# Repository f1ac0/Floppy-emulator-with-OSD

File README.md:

# Floppy emulator with OSD
This is a fusion of a "Gotek" and a "Bluepill" that can provide both FlashFloppy and FF_OSD on a single board. Thank you to Keir Fraser for his firmware https://github.com/keirf/FlashFloppy, and to the chinese people for the original device.

Thanks to the OSD and Amiga keyboard support, LCD/OLED display or buttons are no longer necessary and the device can be almost completely hidden inside Amiga computers, without damaging their case. It is still possible to install a display and buttons, though.

This board also has something special : when connected to an "Amiga dual floppy selector" board, it can daisy-chain between the original floppy drive and the motherboard. In this configuration, the OSD let you choose dynamically which drive is DF0 and DF1. Thanks to this you can enjoy both your original games on floppies and disk images on USB or SDcard !

# Disclaimer
This is a hobbyist project, it comes with no warranty and no support. Also remember that the Amiga machines are about 30 years old and may fail because of such hardware expansions.

This version is not endorsed by the author of FlashFloppy, please don't bother him with issues you might have because of it.

I publish my work under the CC-BY-NC-SA license. The content of this repository is the result of weeks of work, requiring investment in tools, parts, prototypes, and risky tests on his own equipment. For this reason the author does not want third parties to sell products and keep all the profit, usually without even offering support to their customers. If you see people selling this without the consent of the author, don't buy from them.

My modifications to the FF_OSD source are under "the unlicense", like the original code.

If you find it useful and want to reward me : I am always looking for Amiga/Amstrad CPC hardware to repair and hack, please contact me.

# BOM
- 1x STM32F105RBT6
- 1x STM32F103C8T6
- 1x 74LS07D
- 1x 3.3v LDO, either SPX3819M5-L-3-3 or XC6206P332MR or equivalent
- 2x 8MHz HC-49 crystals
- 3x 10uF 0805 capacitors
- 9x 100nF 0805 capacitors
- 4x 22pf 0805 capacitors
- 2x 1k 4x0603 resistor arrays
- 3x 4k7 0805 resistors
- 1x 270 ohm 0805 resistor
- 2x 22 ohm 0805 resistors
- optional for activity LED : 1x 0805 resistor and LED
- 1x 2x17 pins, socket or header, see below. Remove pin 3 which is a key.
- optional for drive daisy-chain : 1x 2x17 pins header or socket. You might choose 90° angled type. Remove pin 3 which is a key.
- 1x USB A Female Socket, type G54
- 1x vertical floppy power connector or 1x4 pin header
- jumpers or wire for DS0/DS1 selection
- pin headers or wires for keyboard, video, drive selection, piezo transducer, SD-card, buttons, rotary encoder, display

Other boards you may use with this "Floppy emulator with OSD":
- [Amiga-dual-floppy-selector](https://github.com/f1ac0/Amiga-dual-floppy-selector) to keep your mechanical drive
- [A600-1200KeyboardSocket](https://github.com/f1ac0/Breakout-and-simple-connector-boards) to pick the keyboard signals on an A600 or A1200
- [USB_A or microSD breakout](https://github.com/f1ac0/Breakout-and-simple-connector-boards) to make the flash memory accessible from outside the system

# Making it
Components are SMD, and have quite thin pin pitch. You need to know what you are doing.

You may choose to install the USB and/or SD connector on a remote board, to make them accessible through trapdoors or openings in the case. You may solder buttons, rotary encoder, LED, display and piezo transducer.

Check for shorts at least between 5V, 12V and GND traces before applying power !

The programming port do not need to be soldered since it needs to be programmed just once : you can just hold it in place during the few seconds required for programming.

If you plan to use the "Amiga dual floppy selector":
- on the hardware side, install female pin socket inside P1 and J11 on the bottom of the PCB. This way they will plug on the pin headers of the selector. Otherwise if you plan to use only ribbon cables, then populate them with pin headers on the top. 
- on the software side, you need to compile FF\_OSD from source, with the small modifications proposed in this repository. Use `patch -ru -d FF_OSD-master  < patch` to apply them. FlashFloppy does not require any modification.

To program the F103 uC then the F105 uC, I personally use a STLINK clone dongle with the stlink tool : https://github.com/stlink-org/stlink. Each uC has its own SWDIO/SWDCLK pins.

To connect the wires to components on the A500 motherboard without soldering on it, here is a tip :
- Take a metal pin from the female 2.54mm pin socket, which is shaped as a lyre. The one you removed from pin 3 for example.
- Solder the wire on the pin, where you normally solder it.
- Place the pin inside heat-shrink tube, with only 1mm of metal uncovered from the tips of the lyre.
- Snap the tip on the lyre on the component where you want to connect.

# Using it
- Connect the device either on top of an "Amiga dual floppy selector", or to the floppy ribbon cable and power plug
- When using the "Amiga dual floppy selector", if you plan to use a second drive, then connect its ribbon cable to the daisy chain connector of the Floppy emulator. Connect the drive power cable on the selector.
- Connect CSYNC, KB_CLOCK and KB_DATA to the motherboard as explained in FF_OSD wiki.
- Connect VIDEO to the motherboard. The 270 ohm resistor is now embedded on the latest revision of the board.
- Insert the USB thumb drive or SD-card
- Turn on the Amiga, enjoy.

To change the drives configuration using the "Amiga dual floppy selector" :
- First you should eject all floppies to prevent confusion of the OS.
- Go to the FF_OSD config menu, change the Drive config setting accordingly. Then Use or Save the new settings.
- If you changed from one to two or two to one drive, then you need to reboot for the second drive to be identified or ignored correctly.

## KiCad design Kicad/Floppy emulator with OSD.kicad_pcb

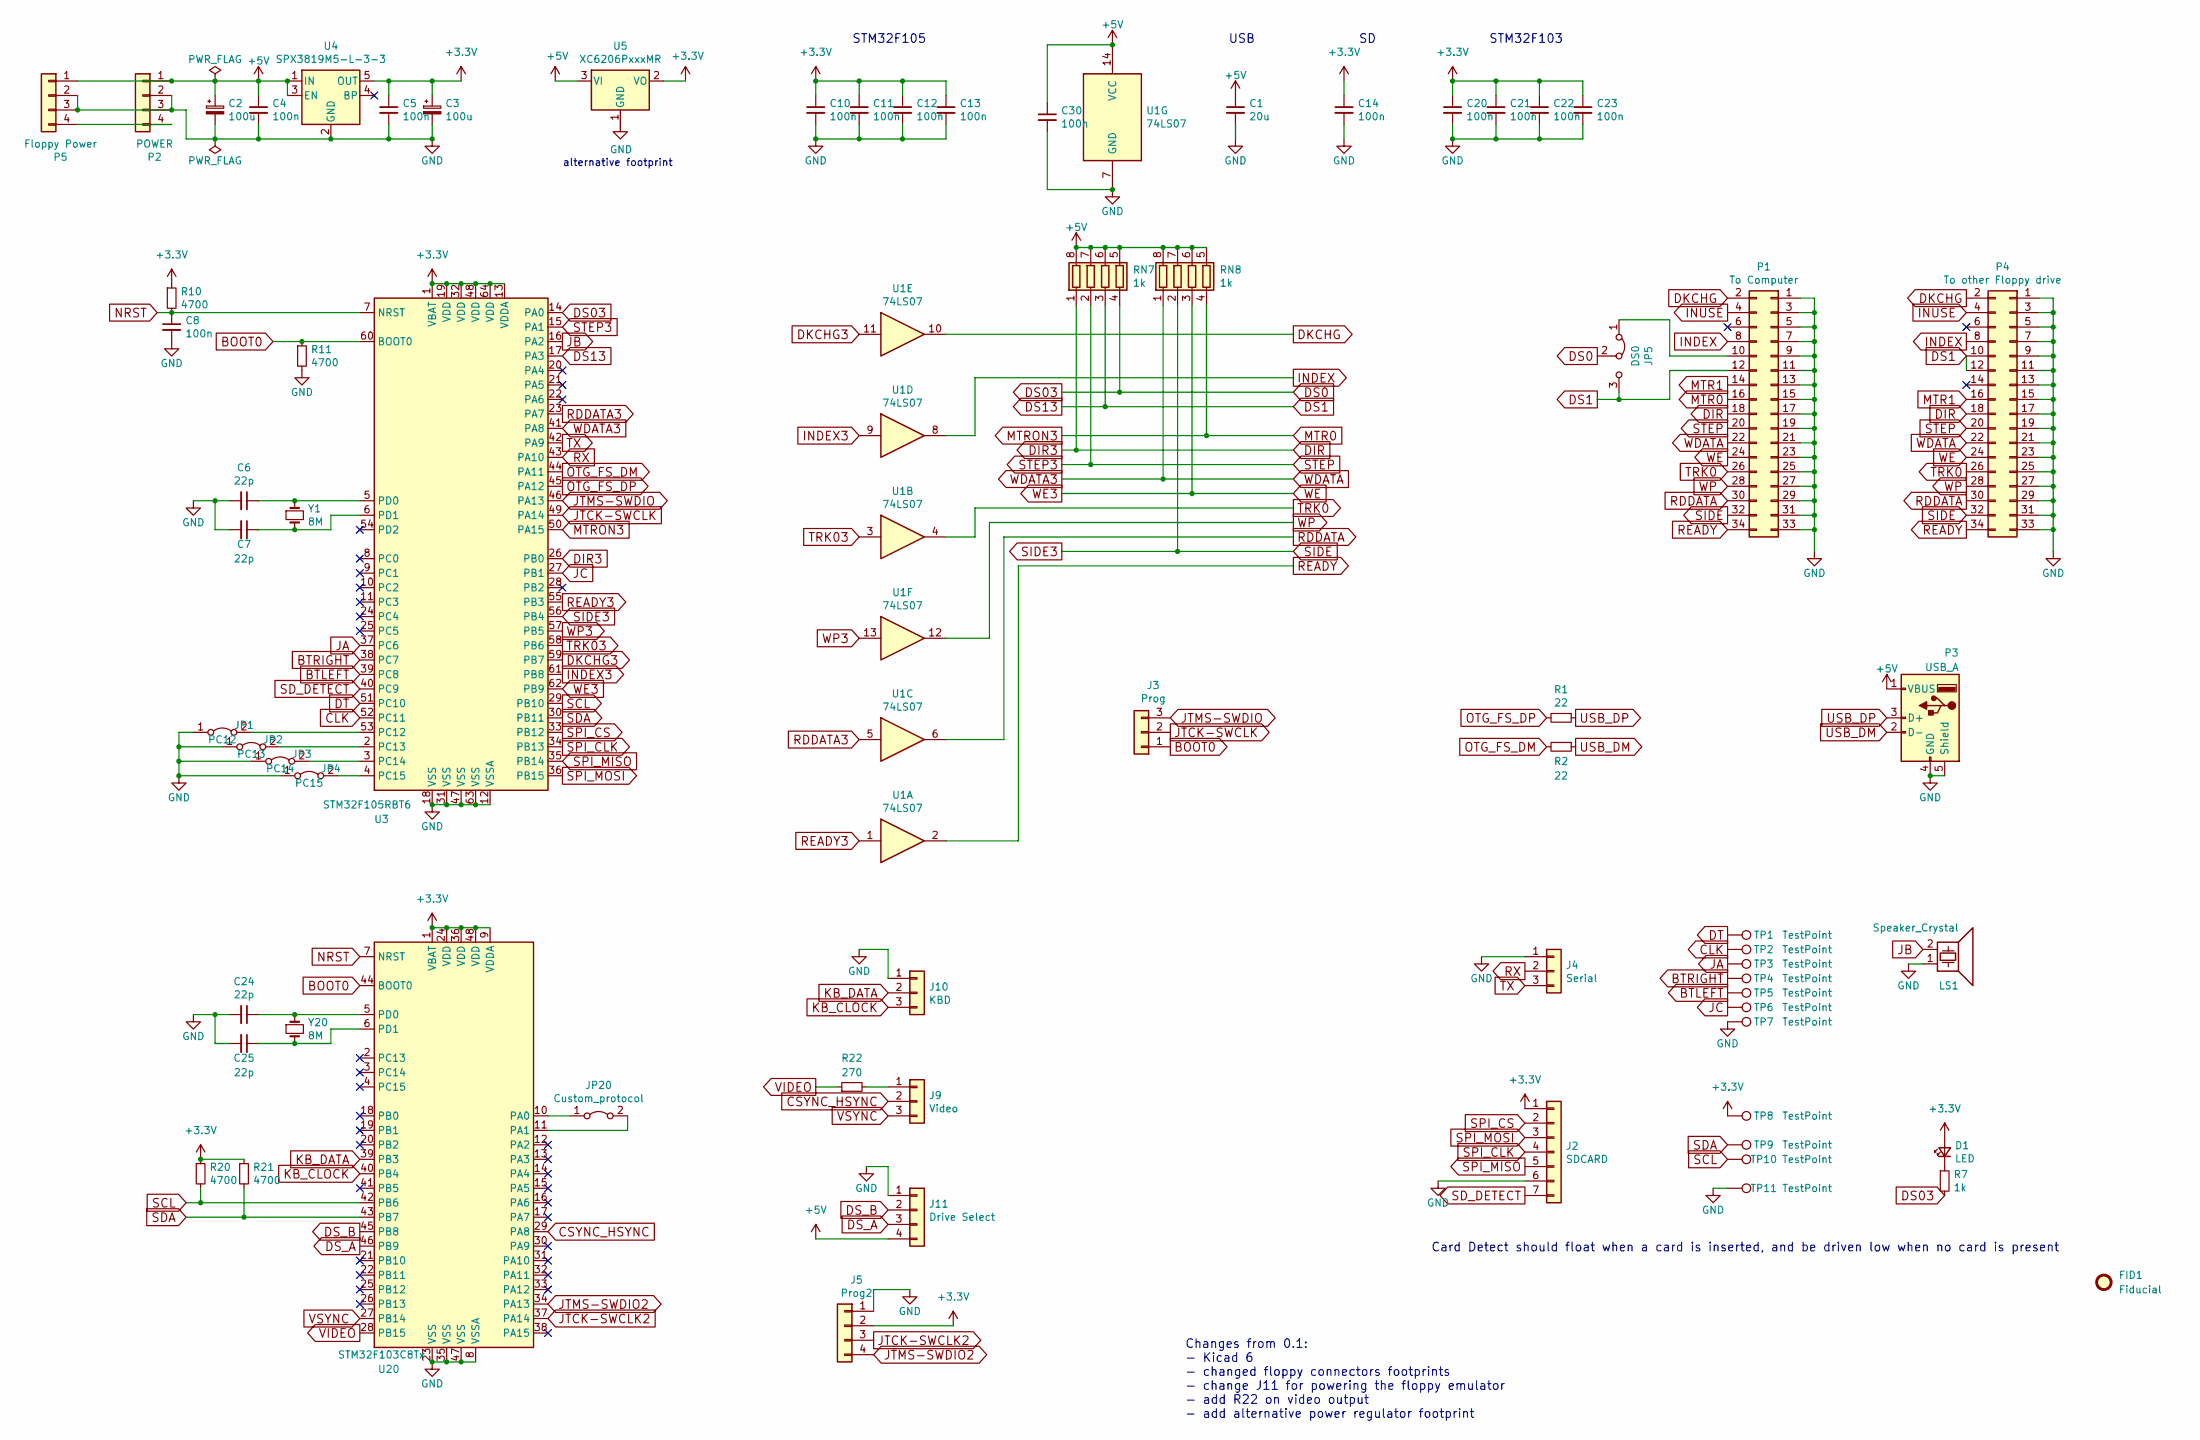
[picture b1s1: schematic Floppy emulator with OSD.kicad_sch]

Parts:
C1: 20u; C_0805_2012Metric
C2, C3: 100u; CP_Radial_D5.0mm_P2.50mm
C4, C5, C8, C10, C11, C12, C13, C14, C20, C21, C22, C23, C30: 100n; C_0805_2012Metric
C6, C7, C24, C25: 22p; C_0805_2012Metric
D1: LED; PinHeader_1x02_P2.54mm_Vertical
FID1: Fiducial; CC_BY_NC_SA_long_silkscreen
J2: SDCARD; PinHeader_1x07_P2.54mm_Vertical
J3: Prog; PinHeader_1x03_P2.54mm_Vertical
J4: Serial; PinHeader_1x03_P2.54mm_Vertical
J5: Prog2; PinHeader_1x04_P2.54mm_Vertical
J9: Video; PinHeader_1x03_P2.54mm_Vertical
J10: KBD; PinHeader_1x03_P2.54mm_Vertical
J11: Drive Select; PinSocket_1x04_P2.54mm_Vertical
JP1: PC12; SolderJumper-2_P1.3mm_Bridged_RoundedPad1.0x1.5mm
JP2: PC13; SolderJumper-2_P1.3mm_Bridged_RoundedPad1.0x1.5mm
JP3: PC14; SolderJumper-2_P1.3mm_Bridged_RoundedPad1.0x1.5mm
JP4: PC15; SolderJumper-2_P1.3mm_Bridged_RoundedPad1.0x1.5mm
JP5: DS0; PinHeader_1x03_P2.54mm_Vertical
JP20: Custom_protocol; SolderJumper-2_P1.3mm_Bridged_RoundedPad1.0x1.5mm
LS1: Speaker_Crystal; PinHeader_1x02_P2.54mm_Vertical
P1: To Computer; PinSocket_2x17_P2.54mm_Vertical
P2: POWER; Floppy_Power_1x04x2.50mm_Vertical
P3: USB_A; USB_A_female_THT_G54
P4: To other Floppy drive; PinHeader_2x17_P2.54mm_Vertical
P5: Floppy Power; PinHeader_1x04_P2.54mm_Vertical
R1, R2: 22; R_0805_2012Metric
R7: 1k; R_0805_2012Metric
R10, R11, R20, R21: 4700; R_0805_2012Metric
R22: 270; R_0805_2012Metric
RN7, RN8: 1k; R_Array_Convex_4x0603
TP1, TP2, TP3, TP4, TP5, TP6, TP7, TP8, TP9, TP10, TP11: TestPoint; TestPoint_THTPad_D1.7mm_Drill1.0mm
U1: 74LS07; SOIC-14_3.9x8.7mm_P1.27mm
U3: STM32F105RBT6; LQFP-64_10x10mm_P0.5mm
U4: SPX3819M5-L-3-3; SOT-23-5
U5: XC6206PxxxMR; SOT-23
U20: STM32F103C8Tx; LQFP-48_7x7mm_P0.5mm
Y1, Y20: 8M; Crystal_HC49-4H_Vertical

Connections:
+3.3V: C3.1, C5.1, C10.1, C11.1, C12.1, C13.1, C14.1, C20.1, C21.1, C22.1, C23.1, D1.2 (A), J2.1, J5.2, R10.1, R20.1, R21.1, TP8.1, U3.1 (VBAT), U3.13 (VDDA), U3.19 (VDD), U3.32 (VDD), U3.48 (VDD), U3.64 (VDD), U4.5 (OUT), U5.2 (VO), U20.1 (VBAT), U20.9 (VDDA), U20.24 (VDD), U20.36 (VDD), U20.48 (VDD)
+5V: C1.1, C2.1, C4.1, C30.1, J11.4, P2.1, P3.1 (VBUS), P5.1, RN7.5 (R4.2), RN7.6 (R3.2), RN7.7 (R2.2), RN7.8 (R1.2), RN8.5 (R4.2), RN8.6 (R3.2), RN8.7 (R2.2), RN8.8 (R1.2), U1.14 (VCC), U4.1 (IN), U4.3 (EN), U5.3 (VI)
BOOT0: J3.1, R11.1, U3.60 (BOOT0), U20.44 (BOOT0)
BTLEFT: TP5.1, U3.39 (PC8)
BTRIGHT: TP4.1, U3.38 (PC7)
CLK: TP2.1, U3.52 (PC11)
CSYNC_HSYNC: J9.2, U20.29 (PA8)
DIR: P1.18, P4.18, RN7.1 (R1.1), U3.26 (PB0)
DKCHG: P1.2, P4.2, U1.10
DKCHG3: U1.11, U3.59 (PB7)
DS0: JP5.2 (C), R7.2, RN7.4 (R4.1), U3.14 (PA0)
DS1: JP5.3 (B), P1.12, P4.10, P4.12, RN7.3 (R3.1), U3.17 (PA3)
DS_A: J11.3, U20.46 (PB9)
DS_B: J11.2, U20.45 (PB8)
DT: TP1.1, U3.51 (PC10)
GND: C1.2, C2.2, C3.2, C4.2, C5.2, C6.2, C7.2, C8.2, C10.2, C11.2, C12.2, C13.2, C14.2, C20.2, C21.2, C22.2, C23.2, C24.2, C25.2, C30.2, J2.6, J4.1, J5.1, J10.1, J11.1, JP1.1 (A), JP2.1 (A), JP3.1 (A), JP4.1 (A), LS1.1, P1.1, P1.3, P1.5, P1.7, P1.9, P1.11, P1.13, P1.15, P1.17, P1.19, P1.21, P1.23, P1.25, P1.27, P1.29, P1.31, P1.33, P2.2, P2.3, P3.4 (GND), P3.5 (Shield), P4.1, P4.3, P4.5, P4.7, P4.9, P4.11, P4.13, P4.15, P4.17, P4.19, P4.21, P4.23, P4.25, P4.27, P4.29, P4.31, P4.33, P5.2, P5.3, R11.2, TP7.1, TP11.1, U1.7 (GND), U3.12 (VSSA), U3.18 (VSS), U3.31 (VSS), U3.47 (VSS), U3.63 (VSS), U4.2 (GND), U5.1 (GND), U20.8 (VSSA), U20.23 (VSS), U20.35 (VSS), U20.47 (VSS)
INDEX: P1.8, P4.8, U1.8
INDEX3: U1.9, U3.61 (PB8)
INUSE: P1.4, P4.4
JA: TP3.1, U3.37 (PC6)
JB: LS1.2, U3.16 (PA2)
JC: TP6.1, U3.27 (PB1)
JTCK-SWCLK: J3.2, U3.49 (PA14)
JTCK-SWCLK2: J5.3, U20.37 (PA14)
JTMS-SWDIO: J3.3, U3.46 (PA13)
JTMS-SWDIO2: J5.4, U20.34 (PA13)
KB_CLOCK: J10.3, U20.40 (PB4)
KB_DATA: J10.2, U20.39 (PB3)
MTR0: P1.16, RN8.4 (R4.1), U3.50 (PA15)
MTR1: P1.14, P4.16
NRST: C8.1, R10.2, U3.7 (NRST), U20.7 (NRST)
unnamed: C6.1, U3.5 (PD0), Y1.1
unnamed: C7.1, U3.6 (PD1), Y1.2
unnamed: C24.1, U20.5 (PD0), Y20.1
unnamed: C25.1, U20.6 (PD1), Y20.2
unnamed: D1.1 (K), R7.1
unnamed: J9.1, R22.2
unnamed: JP1.2 (B), U3.53 (PC12)
unnamed: JP2.2 (B), U3.2 (PC13)
unnamed: JP3.2 (B), U3.3 (PC14)
unnamed: JP4.2 (B), U3.4 (PC15)
unnamed: JP5.1 (A), P1.10
unnamed: JP20.1 (A), U20.10 (PA0)
unnamed: JP20.2 (B), U20.11 (PA1)
unnamed: P2.4, P5.4
OTG_FS_DM: R2.2, U3.44 (PA11)
OTG_FS_DP: R1.2, U3.45 (PA12)
RDDATA: P1.30, P4.30, U1.6
RDDATA3: U1.5, U3.23 (PA7)
READY: P1.34, P4.34, U1.2
READY3: U1.1, U3.55 (PB3)
RX: J4.2, U3.43 (PA10)
SCL: R20.2, TP10.1, U3.29 (PB10), U20.42 (PB6)
SDA: R21.2, TP9.1, U3.30 (PB11), U20.43 (PB7)
SD_DETECT: J2.7, U3.40 (PC9)
SIDE: P1.32, P4.32, RN8.2 (R2.1), U3.56 (PB4)
SPI_CLK: J2.4, U3.34 (PB13)
SPI_CS: J2.2, U3.33 (PB12)
SPI_MISO: J2.5, U3.35 (PB14)
SPI_MOSI: J2.3, U3.36 (PB15)
STEP: P1.20, P4.20, RN7.2 (R2.1), U3.15 (PA1)
TRK0: P1.26, P4.26, U1.4
TRK03: U1.3, U3.58 (PB6)
TX: J4.3, U3.42 (PA9)
USB_DM: P3.2 (D-), R2.1
USB_DP: P3.3 (D+), R1.1
VIDEO: R22.1, U20.28 (PB15)
VSYNC: J9.3, U20.27 (PB14)
WDATA: P1.22, P4.22, RN8.1 (R1.1), U3.41 (PA8)
WE: P1.24, P4.24, RN8.3 (R3.1), U3.62 (PB9)
WP: P1.28, P4.28, U1.12
WP3: U1.13, U3.57 (PB5)

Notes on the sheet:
USB
Card Detect should float when a card is inserted, and be driven low when no card is present
STM32F103
Changes from 0.1: - Kicad 6 - changed floppy connectors footprints - change J11 for powering the floppy emulator - add R22 on video output - add alternative power regulator footprint
alternative footprint
STM32F105

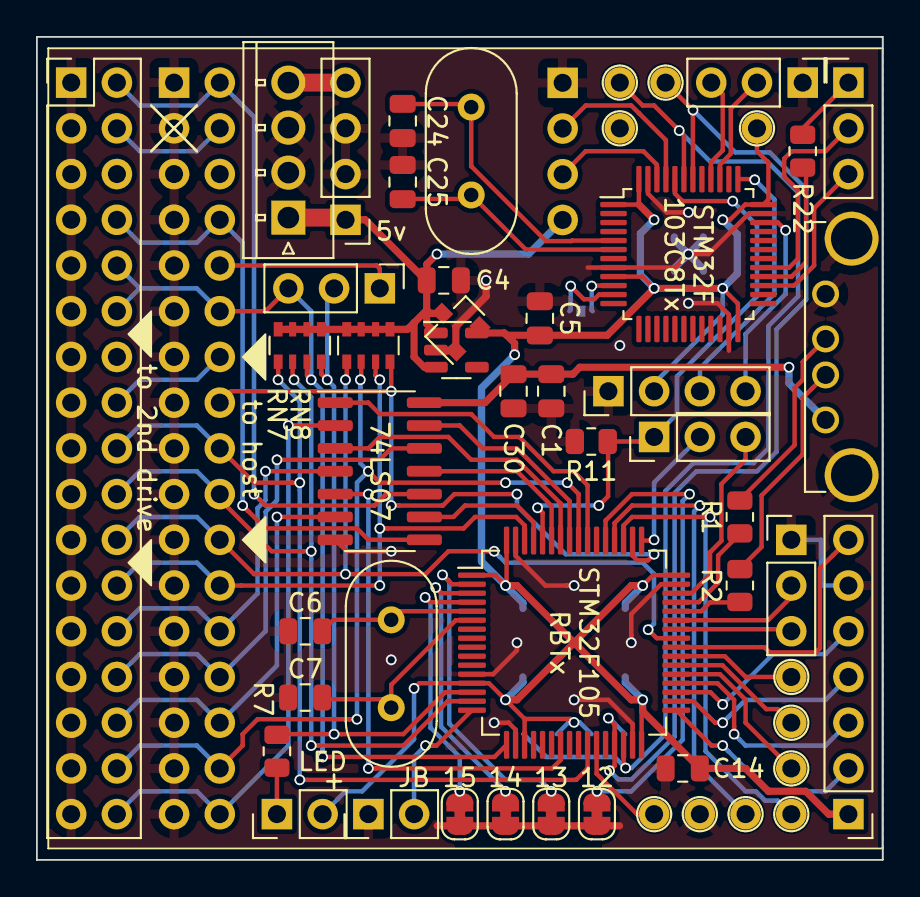
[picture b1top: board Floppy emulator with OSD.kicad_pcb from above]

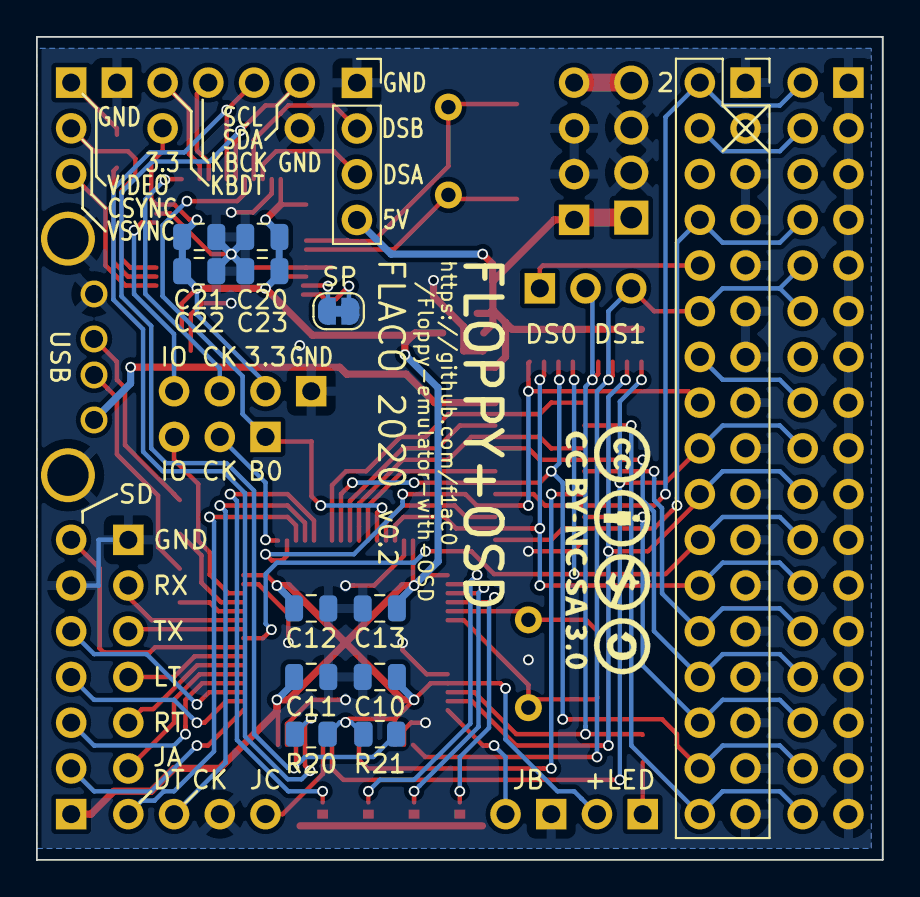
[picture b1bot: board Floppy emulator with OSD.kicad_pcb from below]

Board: 2 copper layers, 47.0 x 45.7 mm, 65 parts (14 on the bottom side), 72 nets.

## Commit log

2020-09-05 Respository init with v0.1 KiCAD files, FF_OSD patch, Readme and License
2022-10-08 Kicad: conversion to Kicad 6, rework component placement to plug on top of selector and include video resistor. Photo
2022-10-13 Public repository init with schematic, Gerbers, ibom, STM32 patch and bin, Photo, Readme, License

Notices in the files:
Kicad/Floppy emulator with OSD.kicad_pcb:
FLACO 2020, licence of this PCB is CC-BY-NC-SA
Kicad/Floppy emulator with OSD.kicad_sch:
FLACO 2020, licence of this schematic is CC-BY-NC-SA
